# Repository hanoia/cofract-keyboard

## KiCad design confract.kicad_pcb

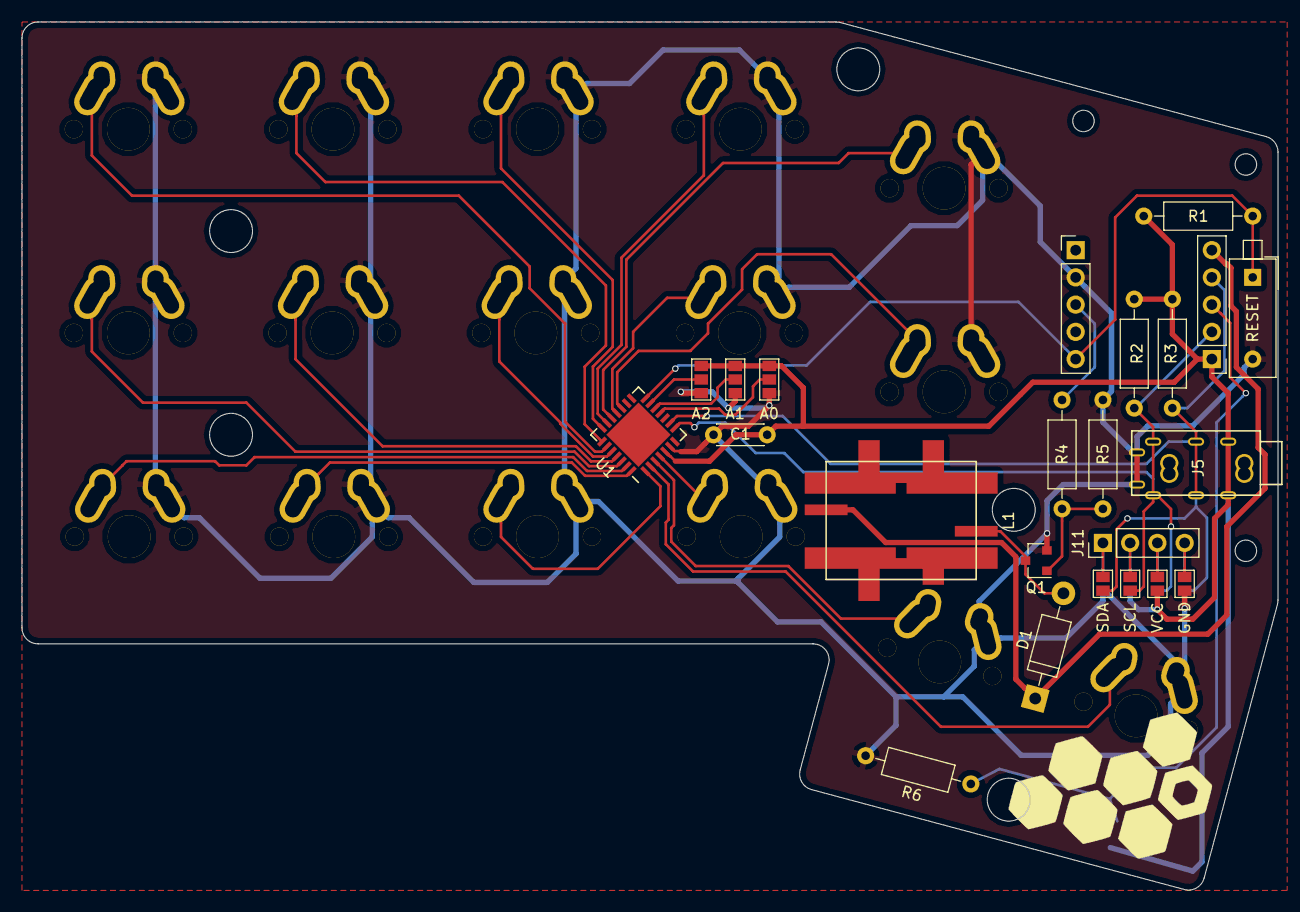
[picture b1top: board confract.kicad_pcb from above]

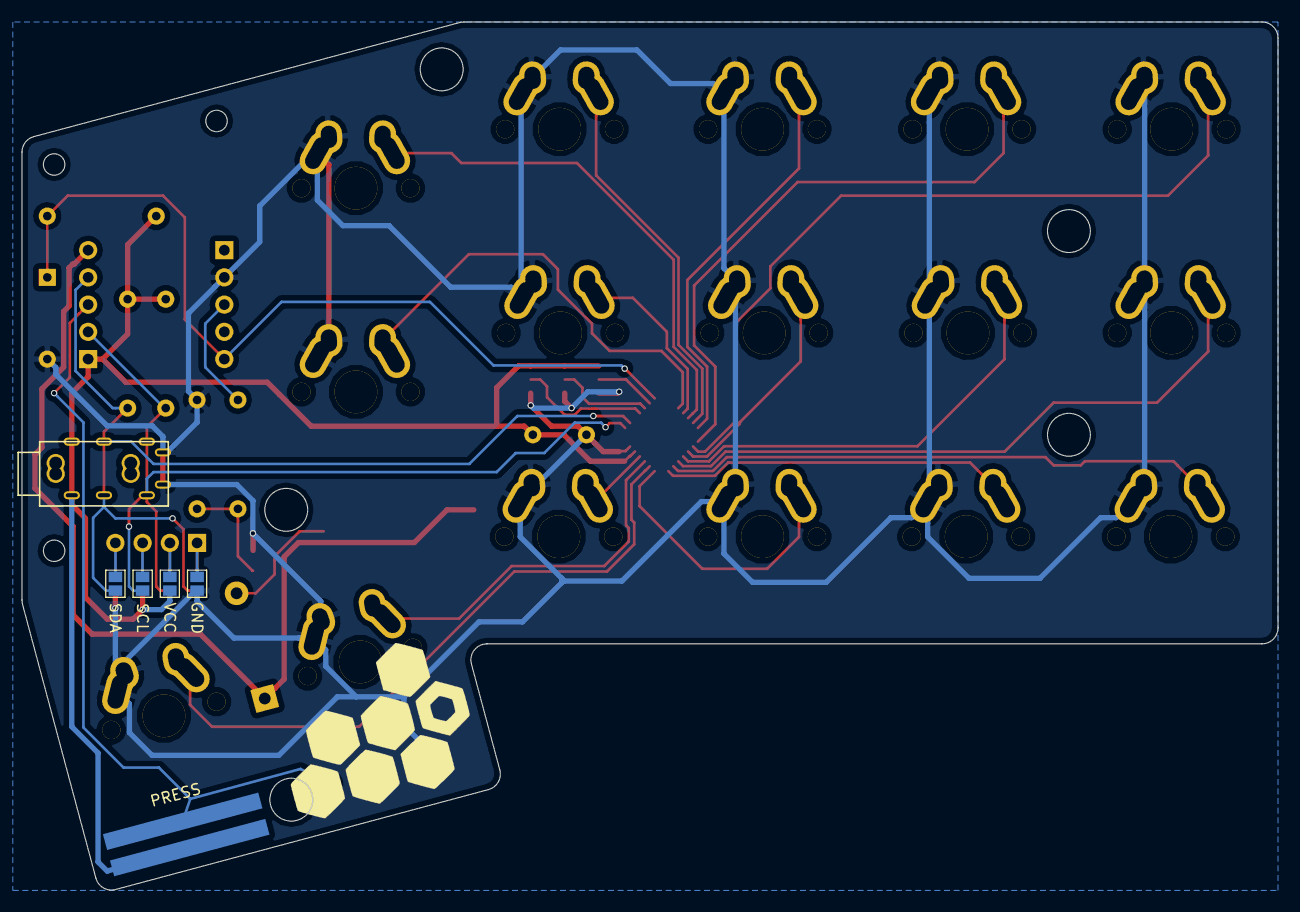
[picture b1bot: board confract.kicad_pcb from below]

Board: 2 copper layers, 117.1 x 81.0 mm, 44 parts (5 on the bottom side), 33 nets.

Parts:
A0, A1, A2: GS3
C1: C; C_Disc_D4.3mm_W1.9mm_P5.00mm
D1: D; D_DO-41_SOD81_P10.16mm_Horizontal
GND: GS2
GND#2: GS2
J1, J3: Conn_01x05; Socket_Strip_Straight_1x05_Pitch2.54mm
J5: Audio-Jack-4; MJ-4PP-9
J11: Conn_01x04; Socket_Strip_Straight_1x04_Pitch2.54mm
L1: LD14-002
PRESS: Conn_01x02; FSR400
Q1: Q_NMOS_GSD; SOT-23
R1, R2, R3, R4, R5, R6: R; R_Axial_DIN0207_L6.3mm_D2.5mm_P10.16mm_Horizontal
RESET: SW_Push; SW_DIP_x1_W7.62mm_Piano
SCL: GS2
SCL#2: GS2
SDA: GS2
SDA#2: GS2
SW2, SW3, SW4, SW5, SW6, SW7, SW8, SW9, SW10, SW11, SW12, SW13, SW14, SW15, SW16, SW17: SW_Push; MXALPS_FLIP
U1: MCP23017_QFN; QFN-28-1EP_6x6mm_Pitch0.65mm
VCC: GS2
VCC#2: GS2

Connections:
Act: J1.3, R4.2
GND: A0.3, A1.3, A2.3, C1.1, GND.1, GND#2.1, J1.2, J5.4, Q1.2, R5.1, R6.2, RESET.2, SW2.2, SW3.2, SW4.2, SW5.2, SW6.2, SW7.2, SW8.2, SW9.2, SW10.2, SW11.2, SW12.2, SW13.2, SW14.2, SW15.2, SW16.2, SW17.2, U1.6
unnamed: D1.2, L1.2, Q1.3
unnamed: A2.2, U1.13
unnamed: A1.2, U1.12
unnamed: A0.2, U1.11
unnamed: GND.2, J11.4, SDA#2.2
unnamed: GND#2.2, J11.1, SDA.2
unnamed: J11.2, SCL.2, VCC#2.2
unnamed: J11.3, SCL#2.2, VCC.2
unnamed: Q1.1, R4.1, R5.2
Press: J3.3, PRESS.2, R6.1
RESET: J1.5, R1.2, RESET.1, U1.14
SCL: J3.2, J5.1, R2.2, SCL.1, SCL#2.1, U1.8
SDA: J3.4, J5.2, R3.2, SDA.1, SDA#2.1, U1.9
SW0: SW2.1, U1.23
SW1: SW5.1, U1.22
SW2: SW8.1, U1.21
SW3: SW11.1, U1.20
SW4: SW14.1, U1.19
SW5: SW3.1, U1.26
SW6: SW6.1, U1.25
SW7: SW9.1, U1.24
SW8: SW12.1, U1.18
SW9: SW15.1, U1.17
SW10: SW4.1, U1.27
SW11: SW7.1, U1.28
SW12: SW10.1, U1.1
SW13: SW13.1, U1.4
SW14: SW16.1, U1.3
SW15: SW17.1, U1.2
VBUS: D1.1, J3.5, L1.1
VCC: A0.1, A1.1, A2.1, C1.2, J3.1, J5.3, PRESS.1, R1.1, R2.1, R3.1, U1.5, VCC.1, VCC#2.1

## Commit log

2018-06-16 add pcb outline
2018-06-16 Init kicad project
2018-06-16 add switches and io expander
2018-06-16 add junctions
2018-06-16 update schematic
2018-06-16 associate components
2018-06-16 load netlist
2018-06-16 load pcb-outline
2018-06-16 place components
2018-06-16 update schematic and pcb
2018-06-16 update silks
2018-06-17 add logo silk
2018-06-17 add gerber
